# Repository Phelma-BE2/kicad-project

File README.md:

# kicad-project
kicad project for the BE, with simulation using ltspice ( nice waveforms ) or ngspice ( ++ foss )

launch the simulation (ltspice)
----------------------------------
- kicad have to be launched in the root of the project or else it will complain that sim/kicaltspice.sh cannot be found.
- open be2.sch in eeschema
 * you can modify/add spice commands in comments blocks beginning with +PSPICE.
- then tools > generate netlist file > Spice tab, fill "simulator command" with sim/kicaltspice.sh and press "Run Simulator".
 * Ltspice will immediately run the simulation and graph plots using the last saved plot configuration file be2.plt.

about sim/kicaltspice.sh
-------------------------
This is a simple wrapper script that makes simulation using kicad a bit less painful. Its main job is to invert pins of diodes to be compatible with spice, discard jacks (K\*\*) and convert suffixes (jumpers JP\*\* becomes xjp\*\*) so they can be simulated with subckts (in sim/lib). Basically it's a bunch of sed and regexp.

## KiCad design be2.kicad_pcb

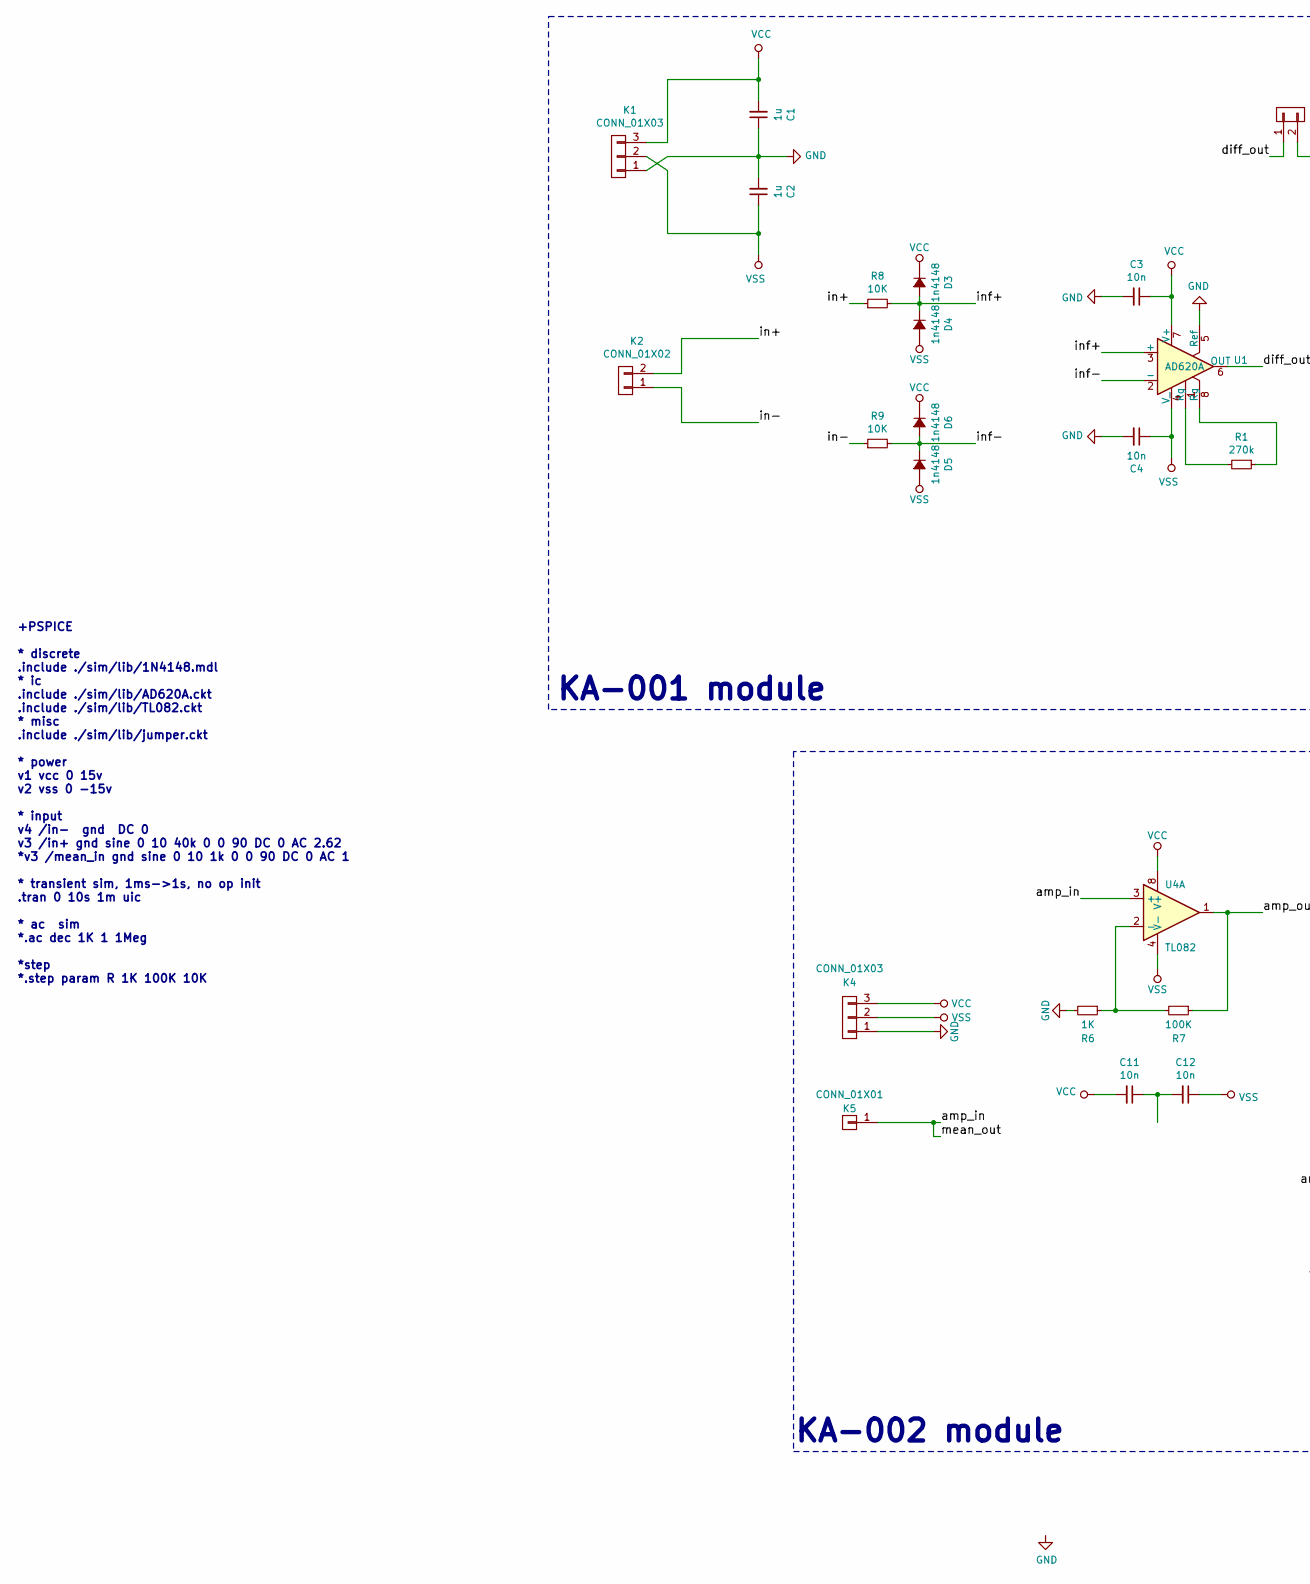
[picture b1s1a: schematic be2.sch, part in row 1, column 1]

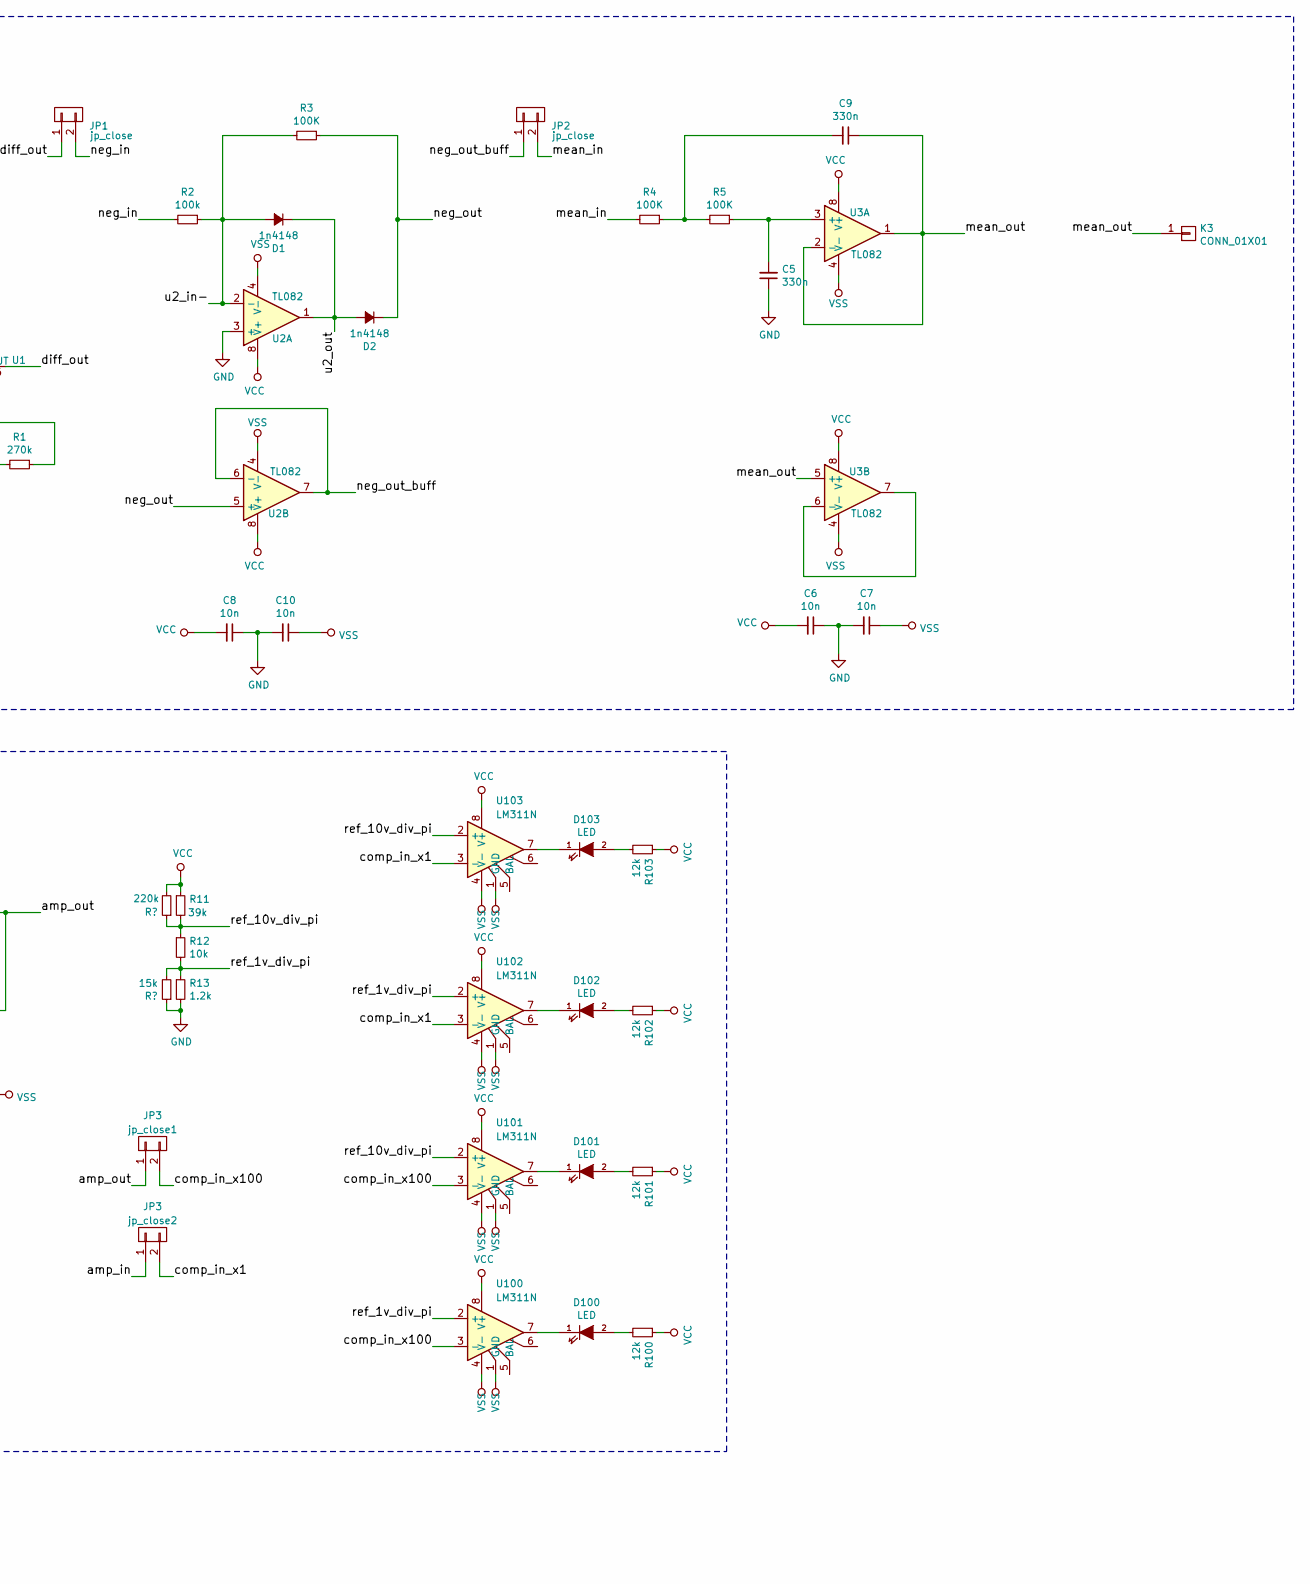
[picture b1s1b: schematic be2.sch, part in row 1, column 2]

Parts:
C1, C2: 1u; C_1206
C3, C4, C6, C7, C8, C10, C11, C12: 10n; C_1206
C5, C9: 330n; C_1206
D1, D2, D3, D4, D5, D6: 1n4148; Diode_DO-41_SOD81_Vertical_AnodeUp_phelma
D100, D101, D102, D103: LED; KP-3216SRC-PRV
JP1, JP2: jp_close; JP_20mil
K1, K4: CONN_01X03; Pin_Header_Straight_1x03_phelma
K2: CONN_01X02; Pin_Header_Straight_1x02_phelma
K3, K5: CONN_01X01; Pin_Header_Straight_1x01_phelma
R1: 270k; R_1206
R2: 100k; R_1206
R3, R4, R5, R7: 100K; R_1206
R6: 1K; R_1206
R8, R9: 10K; R_1206
R11: 39k; R_1206
R12: 10k; R_1206
R13: 1.2k; R_1206
R100, R101, R102, R103: 12k; R_1206
U1: AD620A; SOIC-8_3.9x4.9mm_Pitch1.27mm
U2, U3, U4: TL082; SOIC-8_3.9x4.9mm_Pitch1.27mm
U100, U101, U102, U103: LM311N; SOIC-8_3.9x4.9mm_Pitch1.27mm
jp_close1, jp_close2: JP3; JP_20mil

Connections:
/amp_in: C9.1, K3.1, K5.1, U3.1, U3.2 (-), U3.5 (+), U4.3 (+), jp_close2.1
/amp_out: R7.1, U4.1, jp_close1.1
/comp_in_x1: U102.3 (-), U103.3 (-), jp_close2.2
/comp_in_x100: U100.3 (-), U101.3 (-), jp_close1.2
/diff_out: JP1.1, U1.6 (OUT)
/in+: K2.2, R8.1
/in-: K2.1, R9.1
/inf+: D3.2 (A), D4.1 (K), R8.2, U1.3 (+)
/inf-: D5.1 (K), D6.2 (A), R9.2, U1.2 (-)
/mean_in: JP2.2, R4.2
/neg_in: JP1.2, R2.2
/neg_out: D2.1 (K), R3.1, U2.5 (+)
/neg_out_buff: JP2.1, U2.6 (-), U2.7
/ref_1v_div_pi: R12.2, R13.1, U100.2 (+), U102.2 (+)
/ref_10v_div_pi: R11.2, R12.1, U101.2 (+), U103.2 (+)
/u2_in-: D1.2 (A), R2.1, R3.2, U2.2 (-)
/u2_out: D1.1 (K), D2.2 (A), U2.1
unnamed: C5.2, R5.1, U3.3 (+)
unnamed: C9.2, R4.1, R5.2
unnamed: D100.1 (K), U100.7
unnamed: D100.2 (A), R100.2
unnamed: D101.1 (K), U101.7
unnamed: D101.2 (A), R101.2
unnamed: D102.1 (K), U102.7
unnamed: D102.2 (A), R102.2
unnamed: D103.1 (K), U103.7
unnamed: D103.2 (A), R103.2
unnamed: R1.1, U1.8 (Rg)
unnamed: R1.2, U1.1 (Rg)
unnamed: R6.1, R7.2, U4.2 (-)
unnamed: U3.6 (-), U3.7
VCC: C1.2, C3.1, C6.2, C8.2, C11.2, D3.1 (K), D6.1 (K), K1.3, K4.3, R11.1, R100.1, R101.1, R102.1, R103.1, U1.7 (V+), U2.8 (V+), U3.8 (V+), U4.8 (V+), U100.8 (V+), U101.8 (V+), U102.8 (V+), U103.8 (V+)
VSS: C2.1, C4.1, C7.1, C10.1, C12.1, D4.2 (A), D5.2 (A), K1.2, K4.2, U1.4 (V_), U2.4 (V-), U3.4 (V-), U4.4 (V-), U100.1 (GND), U100.4 (V-), U101.1 (GND), U101.4 (V-), U102.1 (GND), U102.4 (V-), U103.1 (GND), U103.4 (V-)

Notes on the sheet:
+PSPICE * discrete .include ./sim/lib/1N4148.mdl * ic .include ./sim/lib/AD620A.ckt .include ./sim/lib/TL082.ckt * misc .include ./sim/lib/jumper.ckt * power v1 vcc 0 15v v2 vss 0 -15v * input v4 /in- gnd DC 0 v3 /in+ gnd sine 0 10 40k 0 0 90 DC 0 AC 2.62 *v3 /mean_in gnd sine 0 10 1k 0 0 90 DC 0 A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
KA-001 module
KA-002 module

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
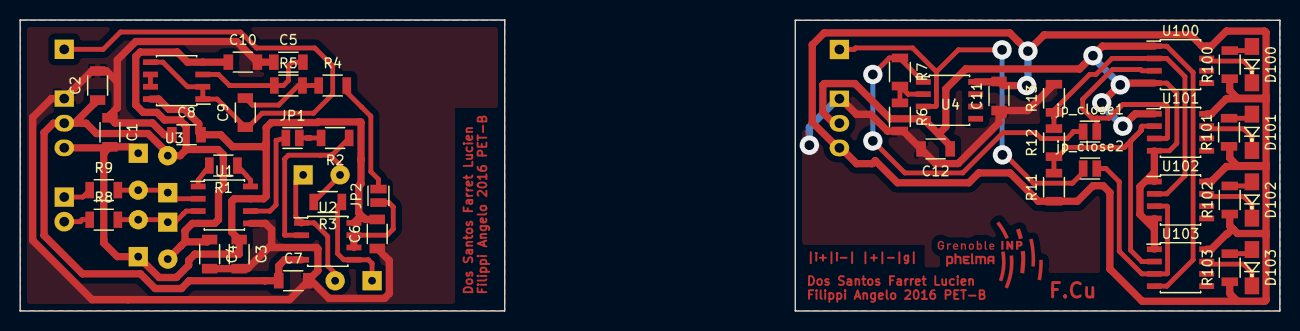
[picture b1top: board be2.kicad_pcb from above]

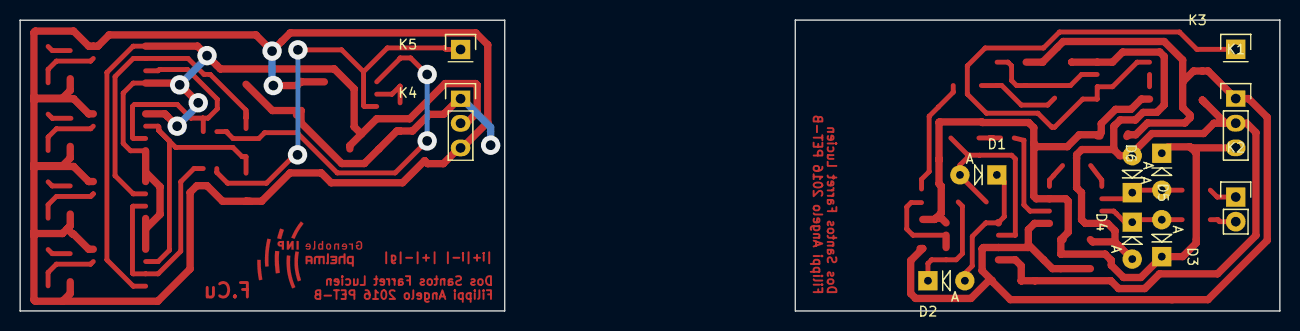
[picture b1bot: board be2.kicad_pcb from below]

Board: 2 copper layers, 130.0 x 30.0 mm, 55 parts (11 on the bottom side), 34 nets.

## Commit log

2016-03-09 initial commit, part1 nearly done, simulation works
2016-03-09 gitignore simulation outputs
2016-03-09 howto simulate
2016-03-11 modifs
2016-03-11 forgot feedback :<
2016-03-11 we're routed, fall back!
2016-03-12 cleaned up the pcb
2016-03-12 through-hole components are now behind the pcb, connectors are aligned on a 0.1 inch grid
2016-03-12 some cleaning on the pcb
2016-03-12 added plot/ output dir
2016-03-13 IOs are now aligned on the same row
2016-03-18 added ltspice wrapper script
2016-04-05 part-1 : final plot in pdf
2016-04-05 tiny correction
2016-04-11 kicost component spreadsheet
2016-05-09 some changes, simu ...
2016-05-09 ugly merge
2016-05-27 part2 + routing
2016-06-02 mechanical drawing
2016-06-02 mechanical drawing : pdf version
2016-06-02 mechanical drawing : png version
2016-06-02 pdf choke on heavy svg ? -> rasterized logo
2016-06-02 stacked render + png output
2016-06-02 better renders ortho(exploded) and persp
2016-06-03 datasheet template
2016-06-03 datasheet++
2016-06-03 datasheet:pinout, cleaned schem
2016-06-03 datasheet:absolute max ratings, schem+pcb:minor modifs
2016-06-03 datasheet:AC+DC caract
2016-06-03 datasheet:over?
2016-06-03 datasheet:output
2016-06-03 added pdf output
